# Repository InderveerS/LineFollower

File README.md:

# LineFollower
Line following robot

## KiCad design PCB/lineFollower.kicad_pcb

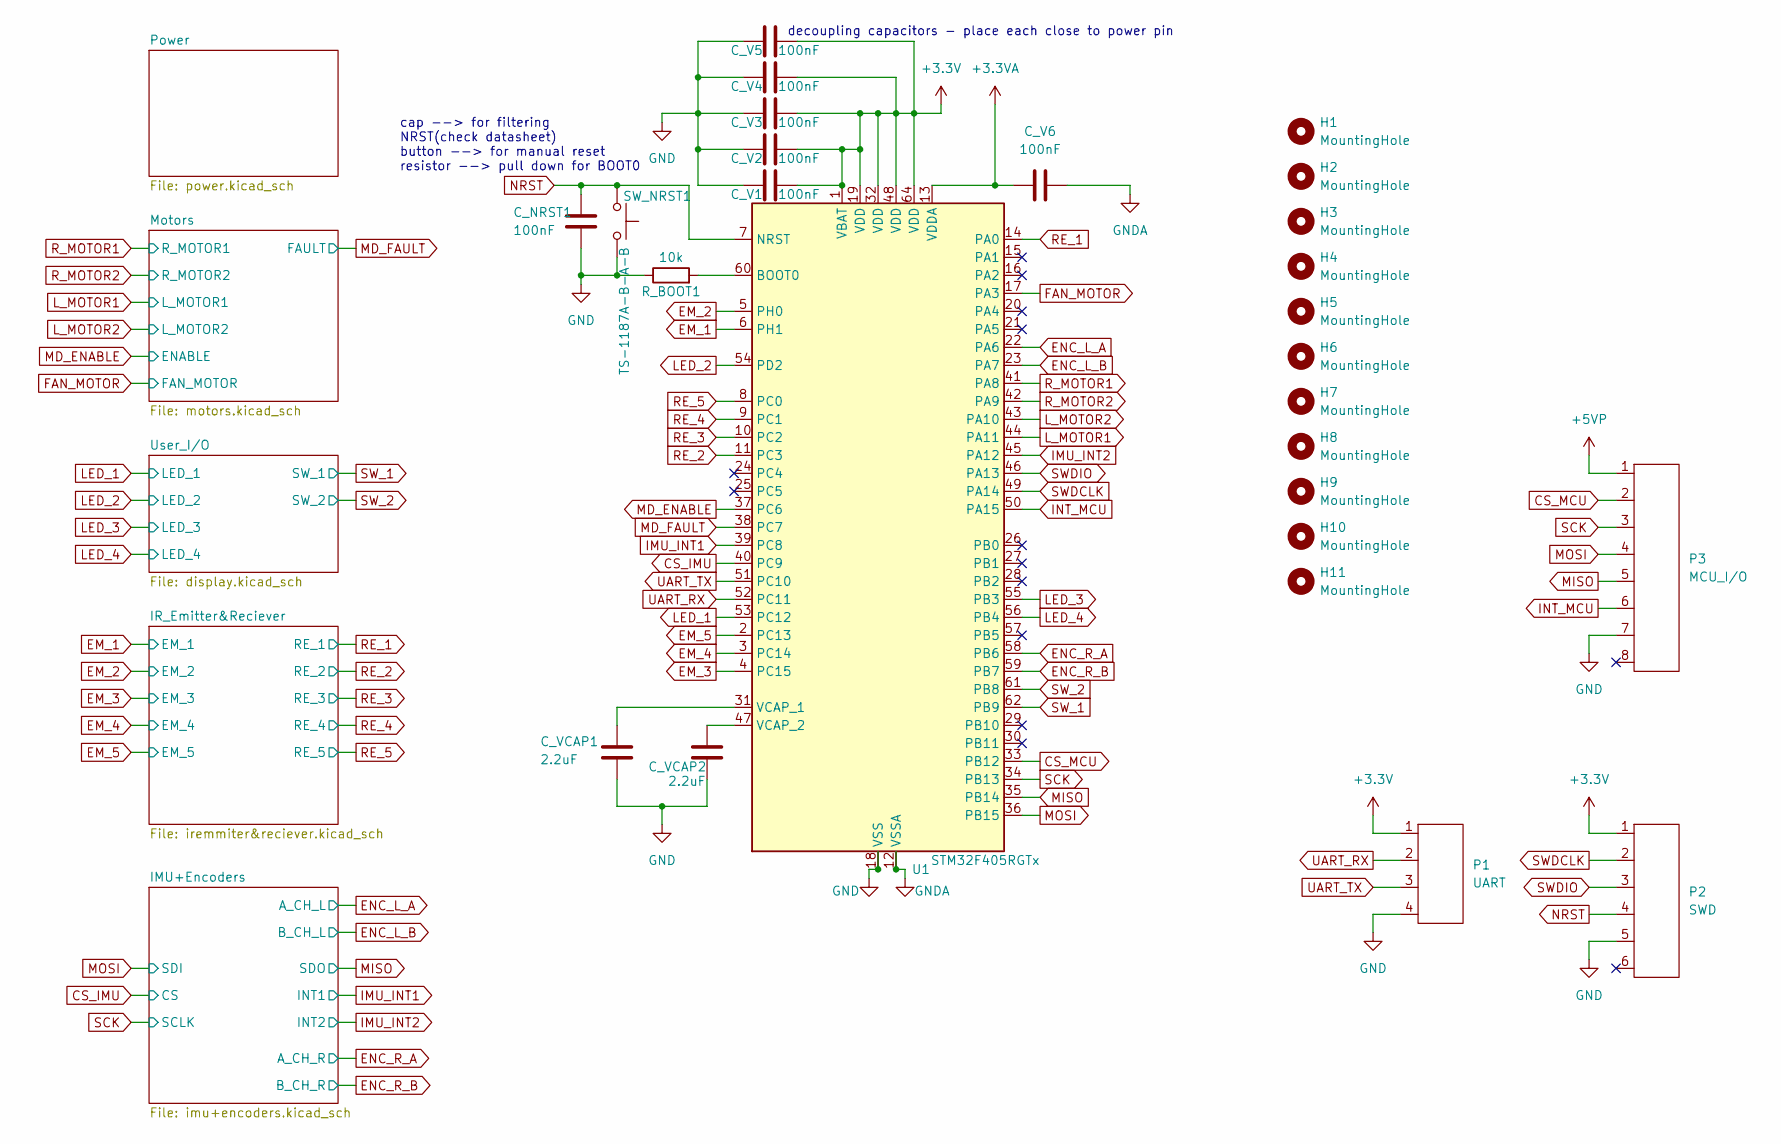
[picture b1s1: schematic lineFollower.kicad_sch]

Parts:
C_NRST1: 100nF; C_0603_1608Metric
C_V1, C_V2, C_V3, C_V4, C_V5, C_V6: 100nF; C_0603_1608Metric
C_VCAP1, C_VCAP2: 2.2uF; C_0603_1608Metric
H1, H2, H3, H4, H5, H6, H7, H8, H9, H10, H11: MountingHole; MountingHole_2.2mm_M2
P1: UART; PinHeader_1x04_P2.54mm_Vertical
P2: SWD; PinHeader_1x06_P2.54mm_Vertical
P3: MCU_I/O; PinHeader_1x08_P2.54mm_Vertical
R_BOOT1: 10k; R_0603_1608Metric
SW_NRST1: TS-1187A-B-A-B
U1: STM32F405RGTx; LQFP-64_10x10mm_P0.5mm

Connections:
+3.3V: C_V1.2, C_V2.2, C_V3.2, C_V4.2, C_V5.2, P1.1, P2.1, U1.1 (VBAT), U1.19 (VDD), U1.32 (VDD), U1.48 (VDD), U1.64 (VDD); also elsewhere on the board
+3.3VA: C_V6.1, U1.13 (VDDA); also elsewhere on the board
+5VP: P3.1; also elsewhere on the board
CS_IMU: U1.40 (PC9); also elsewhere on the board
CS_MCU: P3.2, U1.33 (PB12)
EM_1: U1.6 (PH1); also elsewhere on the board
EM_2: U1.5 (PH0); also elsewhere on the board
EM_3: U1.4 (PC15); also elsewhere on the board
EM_4: U1.3 (PC14); also elsewhere on the board
EM_5: U1.2 (PC13); also elsewhere on the board
ENC_L_A: U1.22 (PA6); also elsewhere on the board
ENC_L_B: U1.23 (PA7); also elsewhere on the board
ENC_R_A: U1.58 (PB6); also elsewhere on the board
ENC_R_B: U1.59 (PB7); also elsewhere on the board
FAN_MOTOR: U1.17 (PA3); also elsewhere on the board
GND: C_NRST1.2, C_V1.1, C_V2.1, C_V3.1, C_V4.1, C_V5.1, C_V6.2, C_VCAP1.2, C_VCAP2.2, P1.4, P2.5, P3.7, R_BOOT1.1, SW_NRST1.2, U1.12 (VSSA), U1.18 (VSS), U1.63 (VSS); also elsewhere on the board
IMU_INT1: U1.39 (PC8); also elsewhere on the board
IMU_INT2: U1.45 (PA12); also elsewhere on the board
INT_MCU: P3.6, U1.50 (PA15)
LED_1: U1.53 (PC12); also elsewhere on the board
LED_2: U1.54 (PD2); also elsewhere on the board
LED_3: U1.55 (PB3); also elsewhere on the board
LED_4: U1.56 (PB4); also elsewhere on the board
L_MOTOR1: U1.44 (PA11); also elsewhere on the board
L_MOTOR2: U1.43 (PA10); also elsewhere on the board
MD_ENABLE: U1.37 (PC6); also elsewhere on the board
MD_FAULT: U1.38 (PC7); also elsewhere on the board
MISO: P3.5, U1.35 (PB14); also elsewhere on the board
MOSI: P3.4, U1.36 (PB15); also elsewhere on the board
NRST: C_NRST1.1, P2.4, SW_NRST1.1, U1.7 (NRST)
unnamed: R_BOOT1.2, U1.60 (BOOT0)
unnamed: C_VCAP1.1, U1.31 (VCAP_1)
unnamed: C_VCAP2.1, U1.47 (VCAP_2)
RE_1: U1.14 (PA0); also elsewhere on the board
RE_2: U1.11 (PC3); also elsewhere on the board
RE_3: U1.10 (PC2); also elsewhere on the board
RE_4: U1.9 (PC1); also elsewhere on the board
RE_5: U1.8 (PC0); also elsewhere on the board
R_MOTOR1: U1.41 (PA8); also elsewhere on the board
R_MOTOR2: U1.42 (PA9); also elsewhere on the board
SCK: P3.3, U1.34 (PB13); also elsewhere on the board
SWDCLK: P2.2, U1.49 (PA14)
SWDIO: P2.3, U1.46 (PA13)
SW_1: U1.62 (PB9); also elsewhere on the board
SW_2: U1.61 (PB8); also elsewhere on the board
UART_RX: P1.2, U1.52 (PC11)
UART_TX: P1.3, U1.51 (PC10)

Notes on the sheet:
decoupling capacitors - place each close to power pin
cap --> for filtering NRST(check datasheet) button --> for manual reset resistor --> pull down for BOOT0

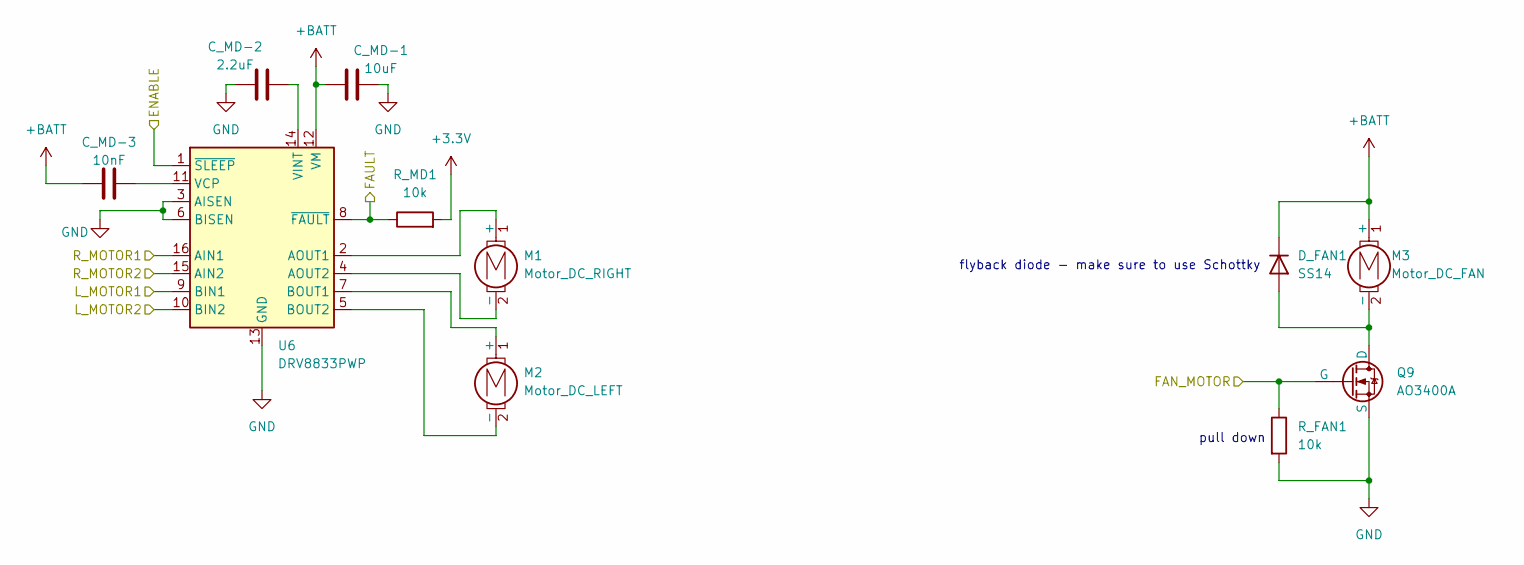
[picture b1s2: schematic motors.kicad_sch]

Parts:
C_MD-1: 10uF; C_0805_2012Metric
C_MD-2: 2.2uF; C_0603_1608Metric
C_MD-3: 10nF; C_0603_1608Metric
D_FAN1: SS14; D_SMA
M1: Motor_DC_RIGHT; PinHeader_1x02_P2.54mm_Vertical
M2: Motor_DC_LEFT; PinHeader_1x02_P2.54mm_Vertical
M3: Motor_DC_FAN; PinHeader_1x02_P2.54mm_Vertical
Q9: AO3400A
R_FAN1: 10k; R_0603_1608Metric
R_MD1: 10k; R_0603_1608Metric
U6: DRV8833PWP; HTSSOP-16-1EP_4.4x5mm_P0.65mm_EP3.4x5mm_Mask2.46x2.31mm_The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

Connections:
+3.3V: R_MD1.2; also elsewhere on the board
+BATT: C_MD-1.1, C_MD-3.1, D_FAN1.1 (K), M3.1 (+), U6.12 (VM); also elsewhere on the board
FAN_MOTOR: Q9.2 (G), R_FAN1.1; also elsewhere on the board
GND: C_MD-1.2, C_MD-2.1, Q9.3 (S), R_FAN1.2, U6.3 (AISEN), U6.6 (BISEN), U6.13 (GND), U6.17 (GND); also elsewhere on the board
L_MOTOR1: U6.9 (BIN1); also elsewhere on the board
L_MOTOR2: U6.10 (BIN2); also elsewhere on the board
MD_ENABLE: U6.1 (~SLEEP); also elsewhere on the board
MD_FAULT: R_MD1.1, U6.8 (~FAULT); also elsewhere on the board
unnamed: D_FAN1.2 (A), M3.2 (-), Q9.1 (D)
unnamed: M1.1 (+), U6.2 (AOUT1)
unnamed: M1.2 (-), U6.4 (AOUT2)
unnamed: M2.1 (+), U6.7 (BOUT1)
unnamed: M2.2 (-), U6.5 (BOUT2)
unnamed: C_MD-3.2, U6.11 (VCP)
unnamed: C_MD-2.2, U6.14 (VINT)
R_MOTOR1: U6.16 (AIN1); also elsewhere on the board
R_MOTOR2: U6.15 (AIN2); also elsewhere on the board

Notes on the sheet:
pull down
flyback diode - make sure to use Schottky

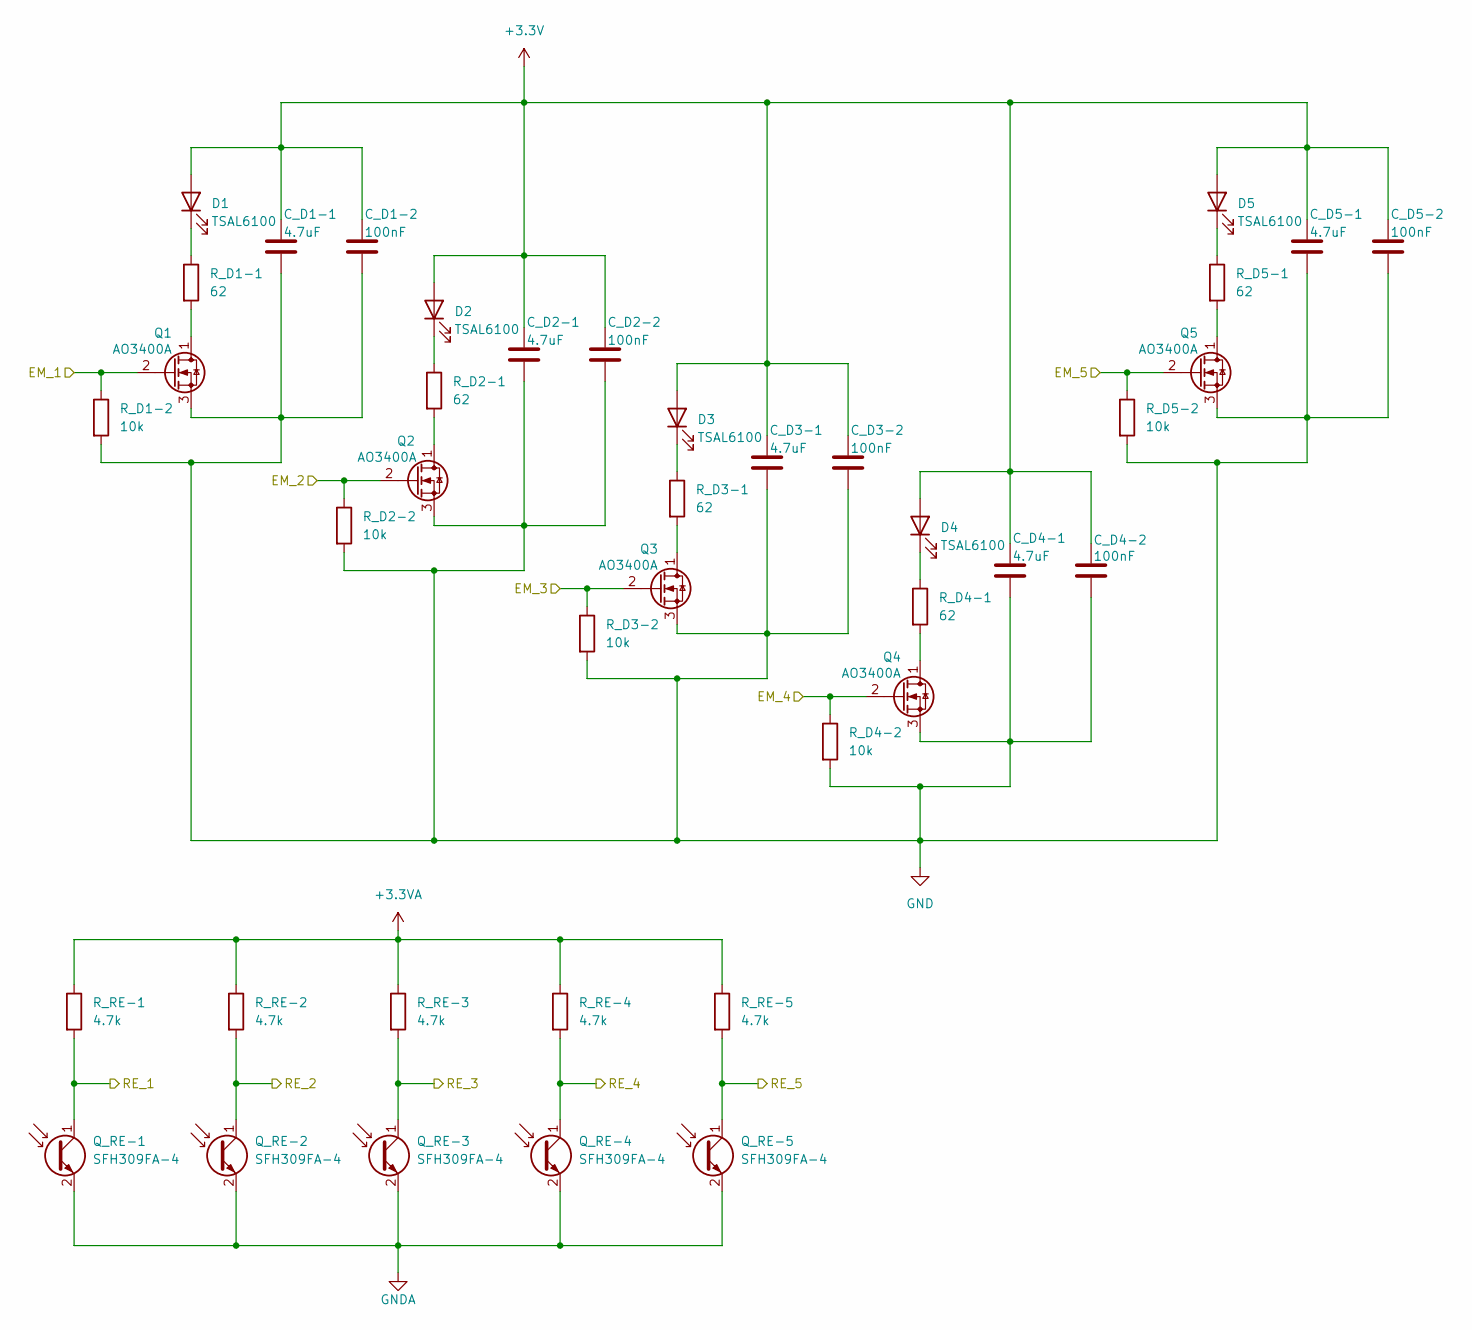
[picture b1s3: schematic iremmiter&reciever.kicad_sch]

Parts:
C_D1-1, C_D2-1, C_D3-1, C_D4-1, C_D5-1: 4.7uF; C_0805_2012Metric
C_D1-2, C_D2-2, C_D3-2, C_D4-2, C_D5-2: 100nF; C_0603_1608Metric
D1, D2, D3, D4, D5: TSAL6100; PinHeader_1x02_P2.54mm_Vertical
Q1, Q2, Q3, Q4, Q5: AO3400A
Q_RE-1, Q_RE-2, Q_RE-3, Q_RE-4, Q_RE-5: SFH309FA-4; PinHeader_1x02_P2.54mm_Vertical
R_D1-1, R_D2-1, R_D3-1, R_D4-1, R_D5-1: 62; R_0603_1608Metric
R_D1-2, R_D2-2, R_D3-2, R_D4-2, R_D5-2: 10k; R_0603_1608Metric
R_RE-1, R_RE-2, R_RE-3, R_RE-4, R_RE-5: 4.7k; R_0603_1608Metric

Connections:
+3.3V: C_D1-1.1, C_D1-2.1, C_D2-1.1, C_D2-2.1, C_D3-1.1, C_D3-2.1, C_D4-1.1, C_D4-2.1, C_D5-1.1, C_D5-2.1, D1.2 (A), D2.2 (A), D3.2 (A), D4.2 (A), D5.2 (A); also elsewhere on the board
+3.3VA: R_RE-1.1, R_RE-2.1, R_RE-3.1, R_RE-4.1, R_RE-5.1; also elsewhere on the board
EM_1: Q1.2 (G), R_D1-2.1; also elsewhere on the board
EM_2: Q2.2 (G), R_D2-2.1; also elsewhere on the board
EM_3: Q3.2 (G), R_D3-2.1; also elsewhere on the board
EM_4: Q4.2 (G), R_D4-2.1; also elsewhere on the board
EM_5: Q5.2 (G), R_D5-2.1; also elsewhere on the board
GND: C_D1-1.2, C_D1-2.2, C_D2-1.2, C_D2-2.2, C_D3-1.2, C_D3-2.2, C_D4-1.2, C_D4-2.2, C_D5-1.2, C_D5-2.2, Q1.3 (S), Q2.3 (S), Q3.3 (S), Q4.3 (S), Q5.3 (S), Q_RE-1.2 (E), Q_RE-2.2 (E), Q_RE-3.2 (E), Q_RE-4.2 (E), Q_RE-5.2 (E), R_D1-2.2, R_D2-2.2, R_D3-2.2, R_D4-2.2, R_D5-2.2; also elsewhere on the board
unnamed: D1.1 (K), R_D1-1.1
unnamed: D2.1 (K), R_D2-1.1
unnamed: D3.1 (K), R_D3-1.1
unnamed: D4.1 (K), R_D4-1.1
unnamed: D5.1 (K), R_D5-1.1
unnamed: Q1.1 (D), R_D1-1.2
unnamed: Q2.1 (D), R_D2-1.2
unnamed: Q3.1 (D), R_D3-1.2
unnamed: Q4.1 (D), R_D4-1.2
unnamed: Q5.1 (D), R_D5-1.2
RE_1: Q_RE-1.1 (C), R_RE-1.2; also elsewhere on the board
RE_2: Q_RE-2.1 (C), R_RE-2.2; also elsewhere on the board
RE_3: Q_RE-3.1 (C), R_RE-3.2; also elsewhere on the board
RE_4: Q_RE-4.1 (C), R_RE-4.2; also elsewhere on the board
RE_5: Q_RE-5.1 (C), R_RE-5.2; also elsewhere on the board

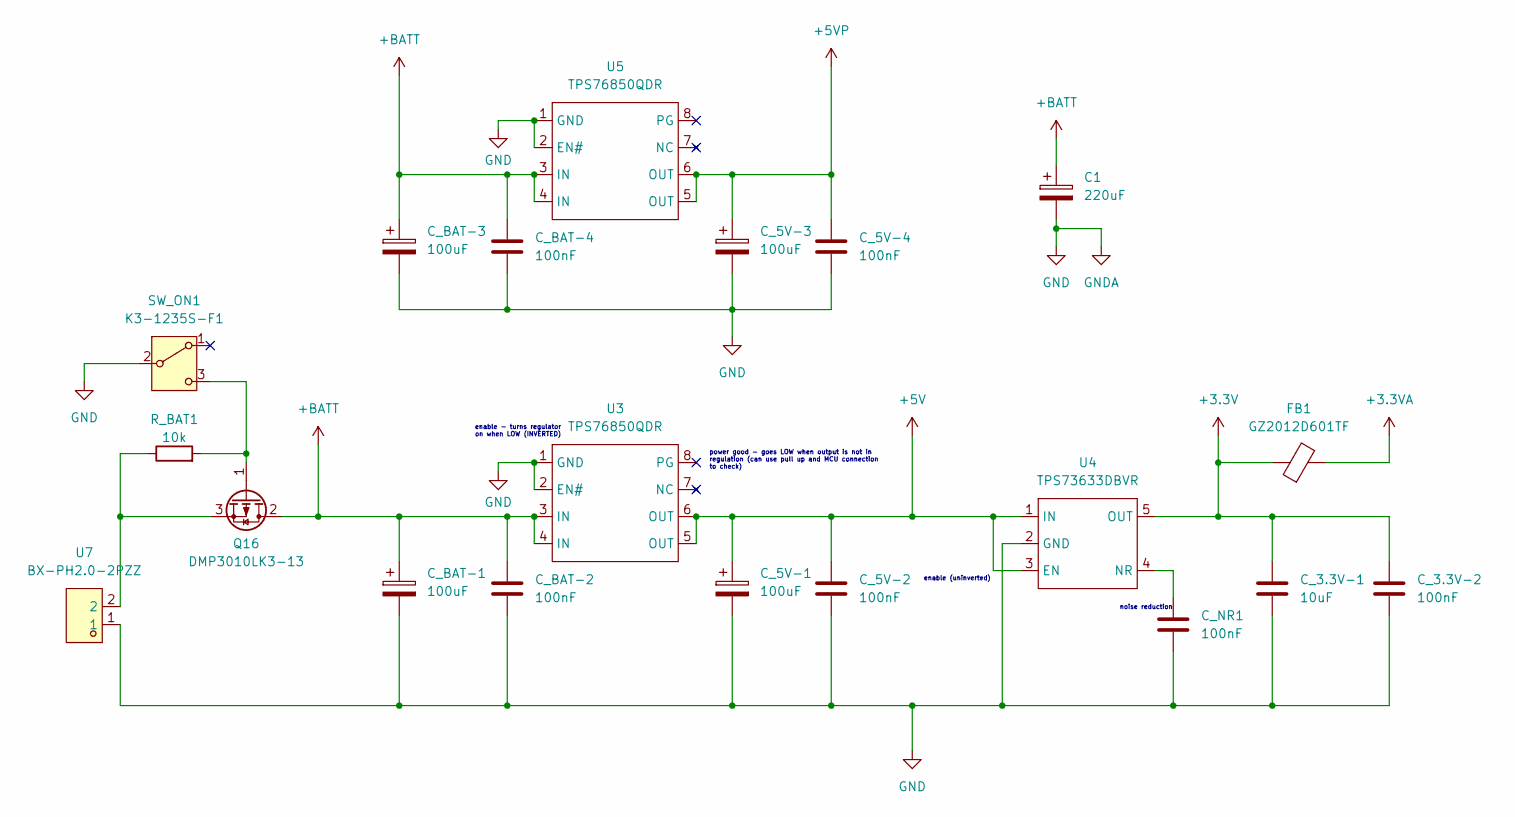
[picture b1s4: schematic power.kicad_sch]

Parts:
C1: 220uF; CP_Elec_8x10
C_3.3V-1: 10uF; C_0805_2012Metric
C_3.3V-2, C_5V-2, C_5V-4: 100nF; C_0603_1608Metric
C_5V-1, C_5V-3: 100uF; CP_Elec_5x5.4
C_BAT-1, C_BAT-3: 100uF; CP_Elec_5x5.4
C_BAT-2, C_BAT-4: 100nF; C_0603_1608Metric
C_NR1: 100nF; C_0603_1608Metric
FB1: GZ2012D601TF; L_0805_2012Metric
Q16: DMP3010LK3-13; TO-252-2
R_BAT1: 10k; R_0603_1608Metric
SW_ON1: K3-1235S-F1
U3, U5: TPS76850QDR; SOIC-8_3.9x4.9mm_P1.27mm
U4: TPS73633DBVR; SOT-23-5
U7: BX-PH2.0-2PZZ; CONN-TH_2P-P2.00_BOSSIE_BX-PH2.0-2PZZ; MPN BX-PH2.0-2PZZ; LCSC Part C18077744

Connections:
+3.3V: C_3.3V-1.1, C_3.3V-2.1, FB1.1, U4.5 (OUT); also elsewhere on the board
+3.3VA: FB1.2; also elsewhere on the board
+5V: C_5V-1.1, C_5V-2.1, U3.5 (OUT), U3.6 (OUT), U4.1 (IN), U4.3 (EN)
+5VP: C_5V-3.1, C_5V-4.1, U5.5 (OUT), U5.6 (OUT); also elsewhere on the board
+BATT: C1.1, C_BAT-1.1, C_BAT-2.1, C_BAT-3.1, C_BAT-4.1, Q16.2 (D), U3.3 (IN), U3.4 (IN), U5.3 (IN), U5.4 (IN); also elsewhere on the board
GND: C1.2, C_3.3V-1.2, C_3.3V-2.2, C_5V-1.2, C_5V-2.2, C_5V-3.2, C_5V-4.2, C_BAT-1.2, C_BAT-2.2, C_BAT-3.2, C_BAT-4.2, C_NR1.2, SW_ON1.2 (B), U3.1 (GND), U3.2 (EN#), U4.2 (GND), U5.1 (GND), U5.2 (EN#), U7.1; also elsewhere on the board
unnamed: Q16.1 (G), R_BAT1.2, SW_ON1.3 (C)
unnamed: Q16.3 (S), R_BAT1.1, U7.2
unnamed: C_NR1.1, U4.4 (NR)

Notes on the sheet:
enable (uninverted)
power good - goes LOW when output is not in regulation (can use pull up and MCU connection to check)
enable - turns regulator on when LOW (INVERTED)
noise reduction

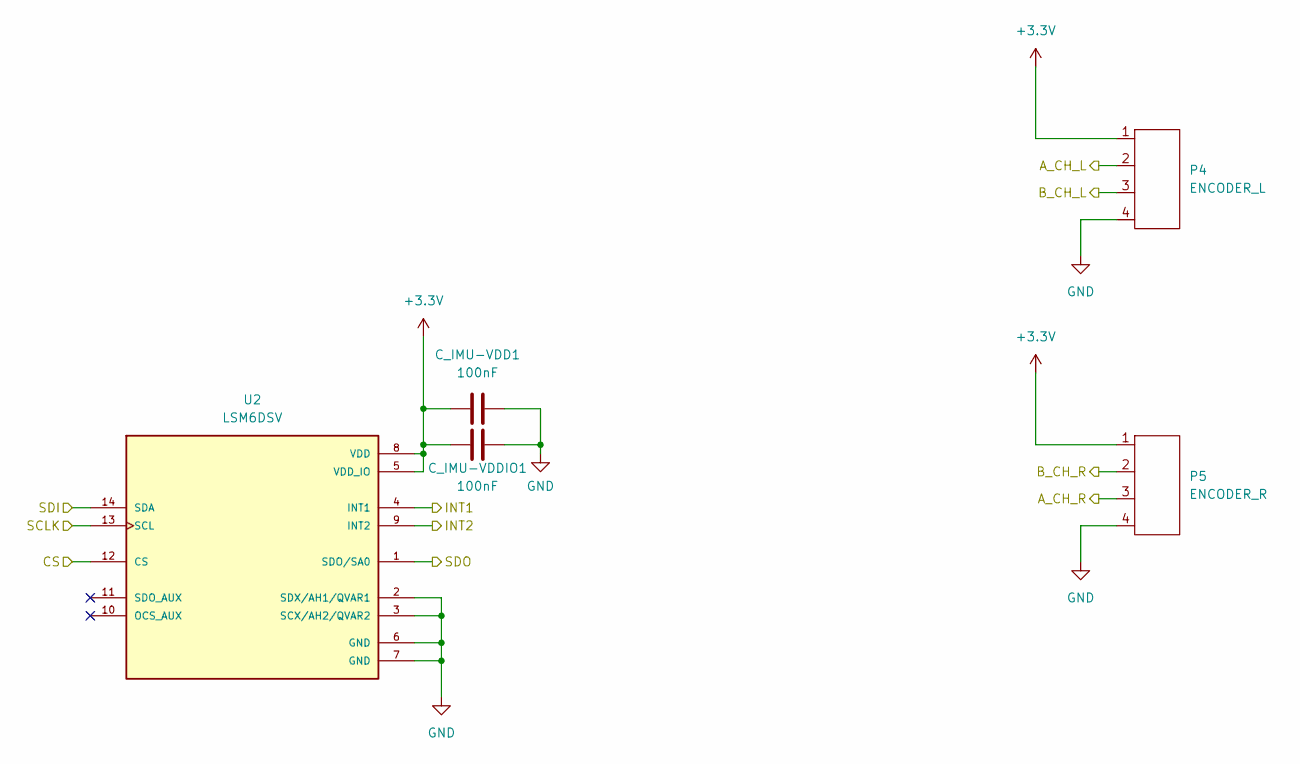
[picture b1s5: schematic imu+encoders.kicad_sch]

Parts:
C_IMU-VDD1: 100nF; C_0603_1608Metric
C_IMU-VDDIO1: 100nF; C_0603_1608Metric
P4: ENCODER_L; PinHeader_1x04_P2.54mm_Vertical
P5: ENCODER_R; PinHeader_1x04_P2.54mm_Vertical
U2: LSM6DSV; XDCR_LSM6DSV

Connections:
+3.3V: C_IMU-VDD1.1, C_IMU-VDDIO1.1, P4.1, P5.1, U2.5 (VDD_IO), U2.8 (VDD); also elsewhere on the board
CS_IMU: U2.12 (CS); also elsewhere on the board
ENC_L_A: P4.2; also elsewhere on the board
ENC_L_B: P4.3; also elsewhere on the board
ENC_R_A: P5.3; also elsewhere on the board
ENC_R_B: P5.2; also elsewhere on the board
GND: C_IMU-VDD1.2, C_IMU-VDDIO1.2, P4.4, P5.4, U2.2 (SDX/AH1/QVAR1), U2.3 (SCX/AH2/QVAR2), U2.6 (GND), U2.7 (GND); also elsewhere on the board
IMU_INT1: U2.4 (INT1); also elsewhere on the board
IMU_INT2: U2.9 (INT2); also elsewhere on the board
MISO: U2.1 (SDO/SA0); also elsewhere on the board
MOSI: U2.14 (SDA); also elsewhere on the board
SCK: U2.13 (SCL); also elsewhere on the board

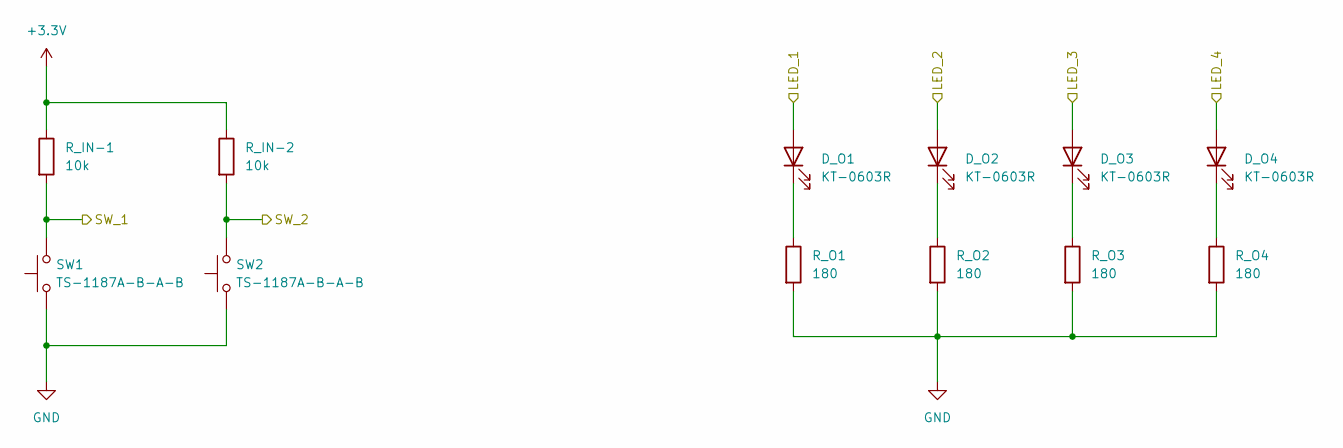
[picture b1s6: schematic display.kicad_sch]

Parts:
D_O1, D_O2, D_O3, D_O4: KT-0603R; LED_0603_1608Metric
R_IN-1, R_IN-2: 10k; R_0603_1608Metric
R_O1, R_O2, R_O3, R_O4: 180; R_0603_1608Metric
SW1, SW2: TS-1187A-B-A-B

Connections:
+3.3V: R_IN-1.1, R_IN-2.1; also elsewhere on the board
GND: R_O1.2, R_O2.2, R_O3.2, R_O4.2, SW1.1, SW2.1; also elsewhere on the board
LED_1: D_O1.2 (A); also elsewhere on the board
LED_2: D_O2.2 (A); also elsewhere on the board
LED_3: D_O3.2 (A); also elsewhere on the board
LED_4: D_O4.2 (A); also elsewhere on the board
unnamed: D_O1.1 (K), R_O1.1
unnamed: D_O2.1 (K), R_O2.1
unnamed: D_O3.1 (K), R_O3.1
unnamed: D_O4.1 (K), R_O4.1
SW_1: R_IN-1.2, SW1.2; also elsewhere on the board
SW_2: R_IN-2.2, SW2.2; also elsewhere on the board

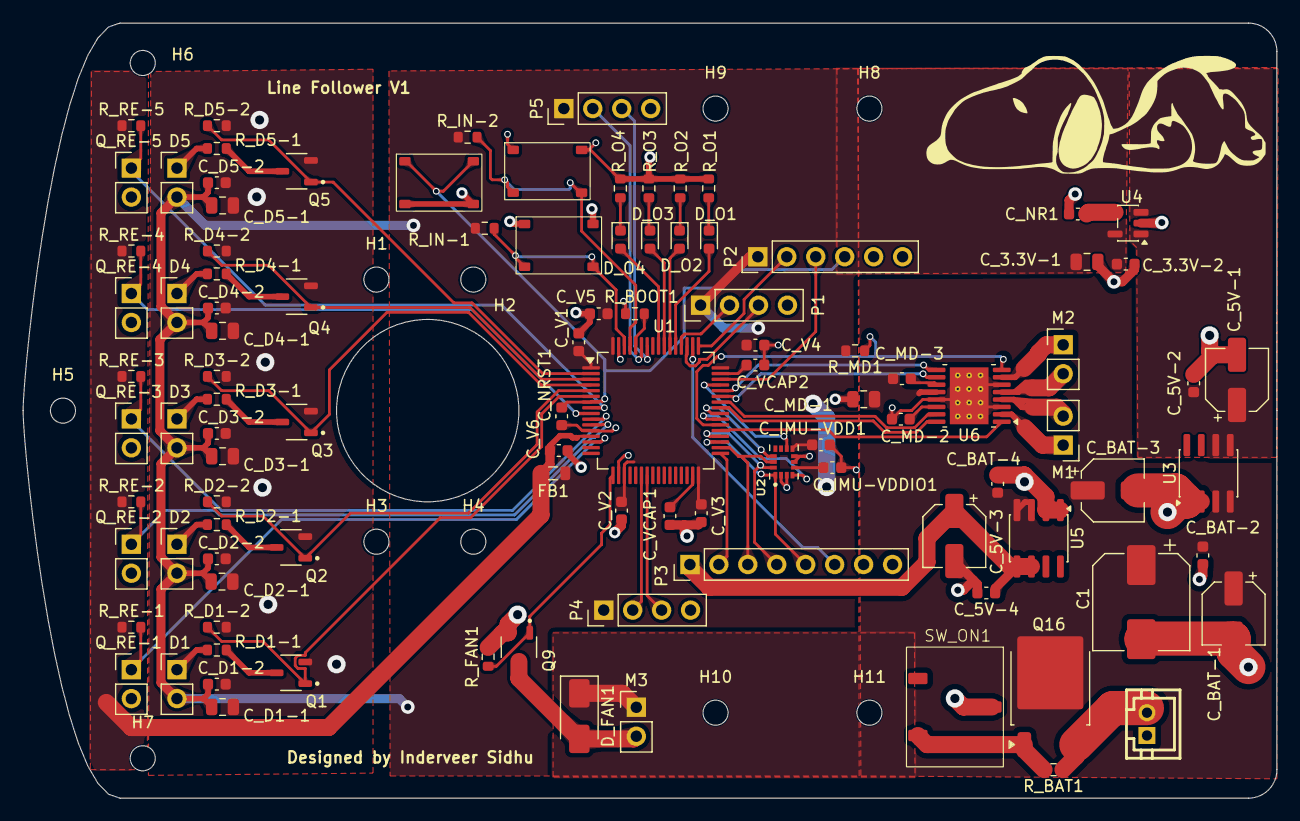
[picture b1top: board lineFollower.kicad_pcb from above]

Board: 2 copper layers, 110.0 x 68.0 mm, 114 parts (0 on the bottom side), 73 nets.

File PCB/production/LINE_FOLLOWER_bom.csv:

Designator,Footprint,Quantity,Value,LCSC Part #
C1,CP_Elec_8x10,1,220uF,
"C_3.3V-1, C_MD-1",0805,2,10uF,
"C_3.3V-2, C_5V-2, C_5V-4, C_BAT-2, C_BAT-4, C_D1-2, C_D2-2, C_D3-2, C_D4-2, C_D5-2, C_IMU-VDD1, C_IMU-VDDIO1, C_NR1, C_NRST1, C_V1, C_V2, C_V3, C_V4, C_V5, C_V6",0603,20,100nF,
"C_5V-1, C_5V-3, C_BAT-1, C_BAT-3",CP_Elec_5x5.4,4,100uF,
"C_D1-1, C_D2-1, C_D3-1, C_D4-1, C_D5-1",0805,5,4.7uF,
"C_MD-2, C_VCAP1, C_VCAP2",0603,3,2.2uF,
C_MD-3,0603,1,10nF,
"D1, D2, D3, D4, D5",PinHeader_1x02_P2.54mm_Vertical,5,TSAL6100,
D_FAN1,D_SMA,1,SS14,
"D_O1, D_O2, D_O3, D_O4",0603,4,KT-0603R,
FB1,0805,1,GZ2012D601TF,
M1,PinHeader_1x02_P2.54mm_Vertical,1,Motor_DC_RIGHT,
M2,PinHeader_1x02_P2.54mm_Vertical,1,Motor_DC_LEFT,
M3,PinHeader_1x02_P2.54mm_Vertical,1,Motor_DC_FAN,
P1,PinHeader_1x04_P2.54mm_Vertical,1,UART,
P2,PinHeader_1x06_P2.54mm_Vertical,1,SWD,
P3,PinHeader_1x08_P2.54mm_Vertical,1,MCU_I/O,
P4,PinHeader_1x04_P2.54mm_Vertical,1,ENCODER_L,
P5,PinHeader_1x04_P2.54mm_Vertical,1,ENCODER_R,
"Q1, Q2, Q3, Q4, Q5, Q9",AO3400A,6,SOT95P280X125-3N,
Q16,TO-252-2,1,DMP3010LK3-13,
"Q_RE-1, Q_RE-2, Q_RE-3, Q_RE-4, Q_RE-5",PinHeader_1x02_P2.54mm_Vertical,5,SFH309FA-4,
"R_BAT1, R_BOOT1, R_D1-2, R_D2-2, R_D3-2, R_D4-2, R_D5-2, R_FAN1, R_IN-1, R_IN-2, R_MD1",0603,11,10k,
"R_D1-1, R_D2-1, R_D3-1, R_D4-1, R_D5-1",0603,5,62,
"R_O1, R_O2, R_O3, R_O4",0603,4,180,
"R_RE-1, R_RE-2, R_RE-3, R_RE-4, R_RE-5",0603,5,4.7k,
"SW1, SW2, SW_NRST1",TS-1187A-B-A-B,3,TS-1187A-B-A-B,
SW_ON1,K3-1235S-F1,1,K3-1235S-F1,
U1,LQFP-64_10x10mm_P0.5mm,1,STM32F405RGTx,
U2,XDCR_LSM6DSV,1,LSM6DSV,
"U3, U5",SOIC-8_3.9x4.9mm_P1.27mm,2,TPS76850QDR,
U4,SOT-23-5,1,TPS73633DBVR,
U6,HTSSOP-16-1EP_4.4x5mm_P0.65mm_EP3.4x5mm_Mask2.46x2.31mm_ThermalVias,1,DRV8833PWP,
U7,CONN-TH_2P-P2.00_BOSSIE_BX-PH2.0-2PZZ,1,BX-PH2.0-2PZZ,C18077744

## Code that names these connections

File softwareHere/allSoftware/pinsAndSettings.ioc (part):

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Mcu.Name=STM32F405RGTx
Mcu.Package=LQFP64
Mcu.UserName=STM32F405RGTx
PA0-WKUP.Signal=ADCx_IN0
PA10.Signal=S_TIM1_CH3
PA11.Signal=S_TIM1_CH4
PA12.Signal=GPIO_Input
PA13.Mode=Serial_Wire
PA13.Signal=SYS_JTMS-SWDIO
PA14.Mode=Serial_Wire
PA14.Signal=SYS_JTCK-SWCLK
PA15.Signal=GPIO_Input
PA3.Signal=S_TIM5_CH4
PA6.Signal=S_TIM3_CH1
PA7.Signal=S_TIM3_CH2
PA8.Signal=S_TIM1_CH1
PA9.Signal=S_TIM1_CH2
PB12.Signal=GPIO_Output
PB13.Mode=Full_Duplex_Master
PB13.Signal=SPI2_SCK
PB14.Mode=Full_Duplex_Master
PB14.Signal=SPI2_MISO
PB15.Mode=Full_Duplex_Master
PB15.Signal=SPI2_MOSI
PB3.Signal=GPIO_Output
PB4.Signal=GPIO_Output
PB6.Signal=S_TIM4_CH1
PB7.Signal=S_TIM4_CH2
PB8.Signal=GPIO_Input
PB9.Signal=GPIO_Input
PC0.Signal=ADCx_IN10
PC1.Signal=ADCx_IN11
PC10.Mode=Asynchronous
PC10.Signal=USART3_TX
PC11.Mode=Asynchronous
PC11.Signal=USART3_RX
PC12.Signal=GPIO_Output
PC13-ANTI_TAMP.Signal=GPIO_Output
PC14-OSC32_IN.Signal=GPIO_Output
PC15-OSC32_OUT.Signal=GPIO_Output
PC2.Signal=ADCx_IN12
PC3.Signal=ADCx_IN13
PC6.Signal=GPIO_Output
PC7.Signal=GPIO_Input
PC8.Signal=GPIO_Input
PC9.Signal=GPIO_Output
PD2.Signal=GPIO_Output
PH0-OSC_IN.Signal=GPIO_Output
PH1-OSC_OUT.Signal=GPIO_Output
RCC.HSE_VALUE=25000000
RCC.SYSCLKFreq_VALUE=168000000
RCC.SYSCLKSource=RCC_SYSCLKSOURCE_PLLCLK
board=custom

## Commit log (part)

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2026-05-06 tweaked 3D Models
2026-05-08 Made data_logging.h file
2026-05-09 madeMotorsWork
2026-05-11 Added Motor encoder data + logging over UART to flash memory
2026-05-11 Add .gitignore to exclude debug and system files
2026-05-18 Add Python script to receive and plot motor data from STM32
2026-05-18 added motor left right control
2026-05-18 motors.h made
2026-05-18 made pid.c
2026-05-18 Add PID controller header file
2026-05-18 Initialize PWM and encoder for TIM1 and TIM3
2026-05-18 implemented logging features
2026-05-18 Refactored motor data handling
2026-05-18 fixed python script
2026-05-18 fixed.
2026-05-19 Added Code to make Logging work
2026-06-01 changed gitignore, added controls and pid files
2026-06-01 updated gitignore again
2026-06-02 finished controller, sensors, and added initialization in main
2026-06-12 added button-triggered logging with LED countdown and auto-stop
2026-06-16 remade so gitignore works
2026-06-21 added tim6
